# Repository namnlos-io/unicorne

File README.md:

# The Unicorne

Current revision: $Id$

A single-piece corne keyboard mod and case.

Unicorne is a Corne keyboard coupled with a hinged unibody case based on ["Corne Travel Case"](https://www.thingiverse.com/thing:4921564) by [denniskempin](https://www.thingiverse.com/denniskempin).

The Corne inside is using a single Pro Micro on the left side and a single display on the right side, the sides are part of the same matrix connected through the center hinge instead of the traditional setup with two Pro Micro's and a TRRS cable connecting the halves.

## Images

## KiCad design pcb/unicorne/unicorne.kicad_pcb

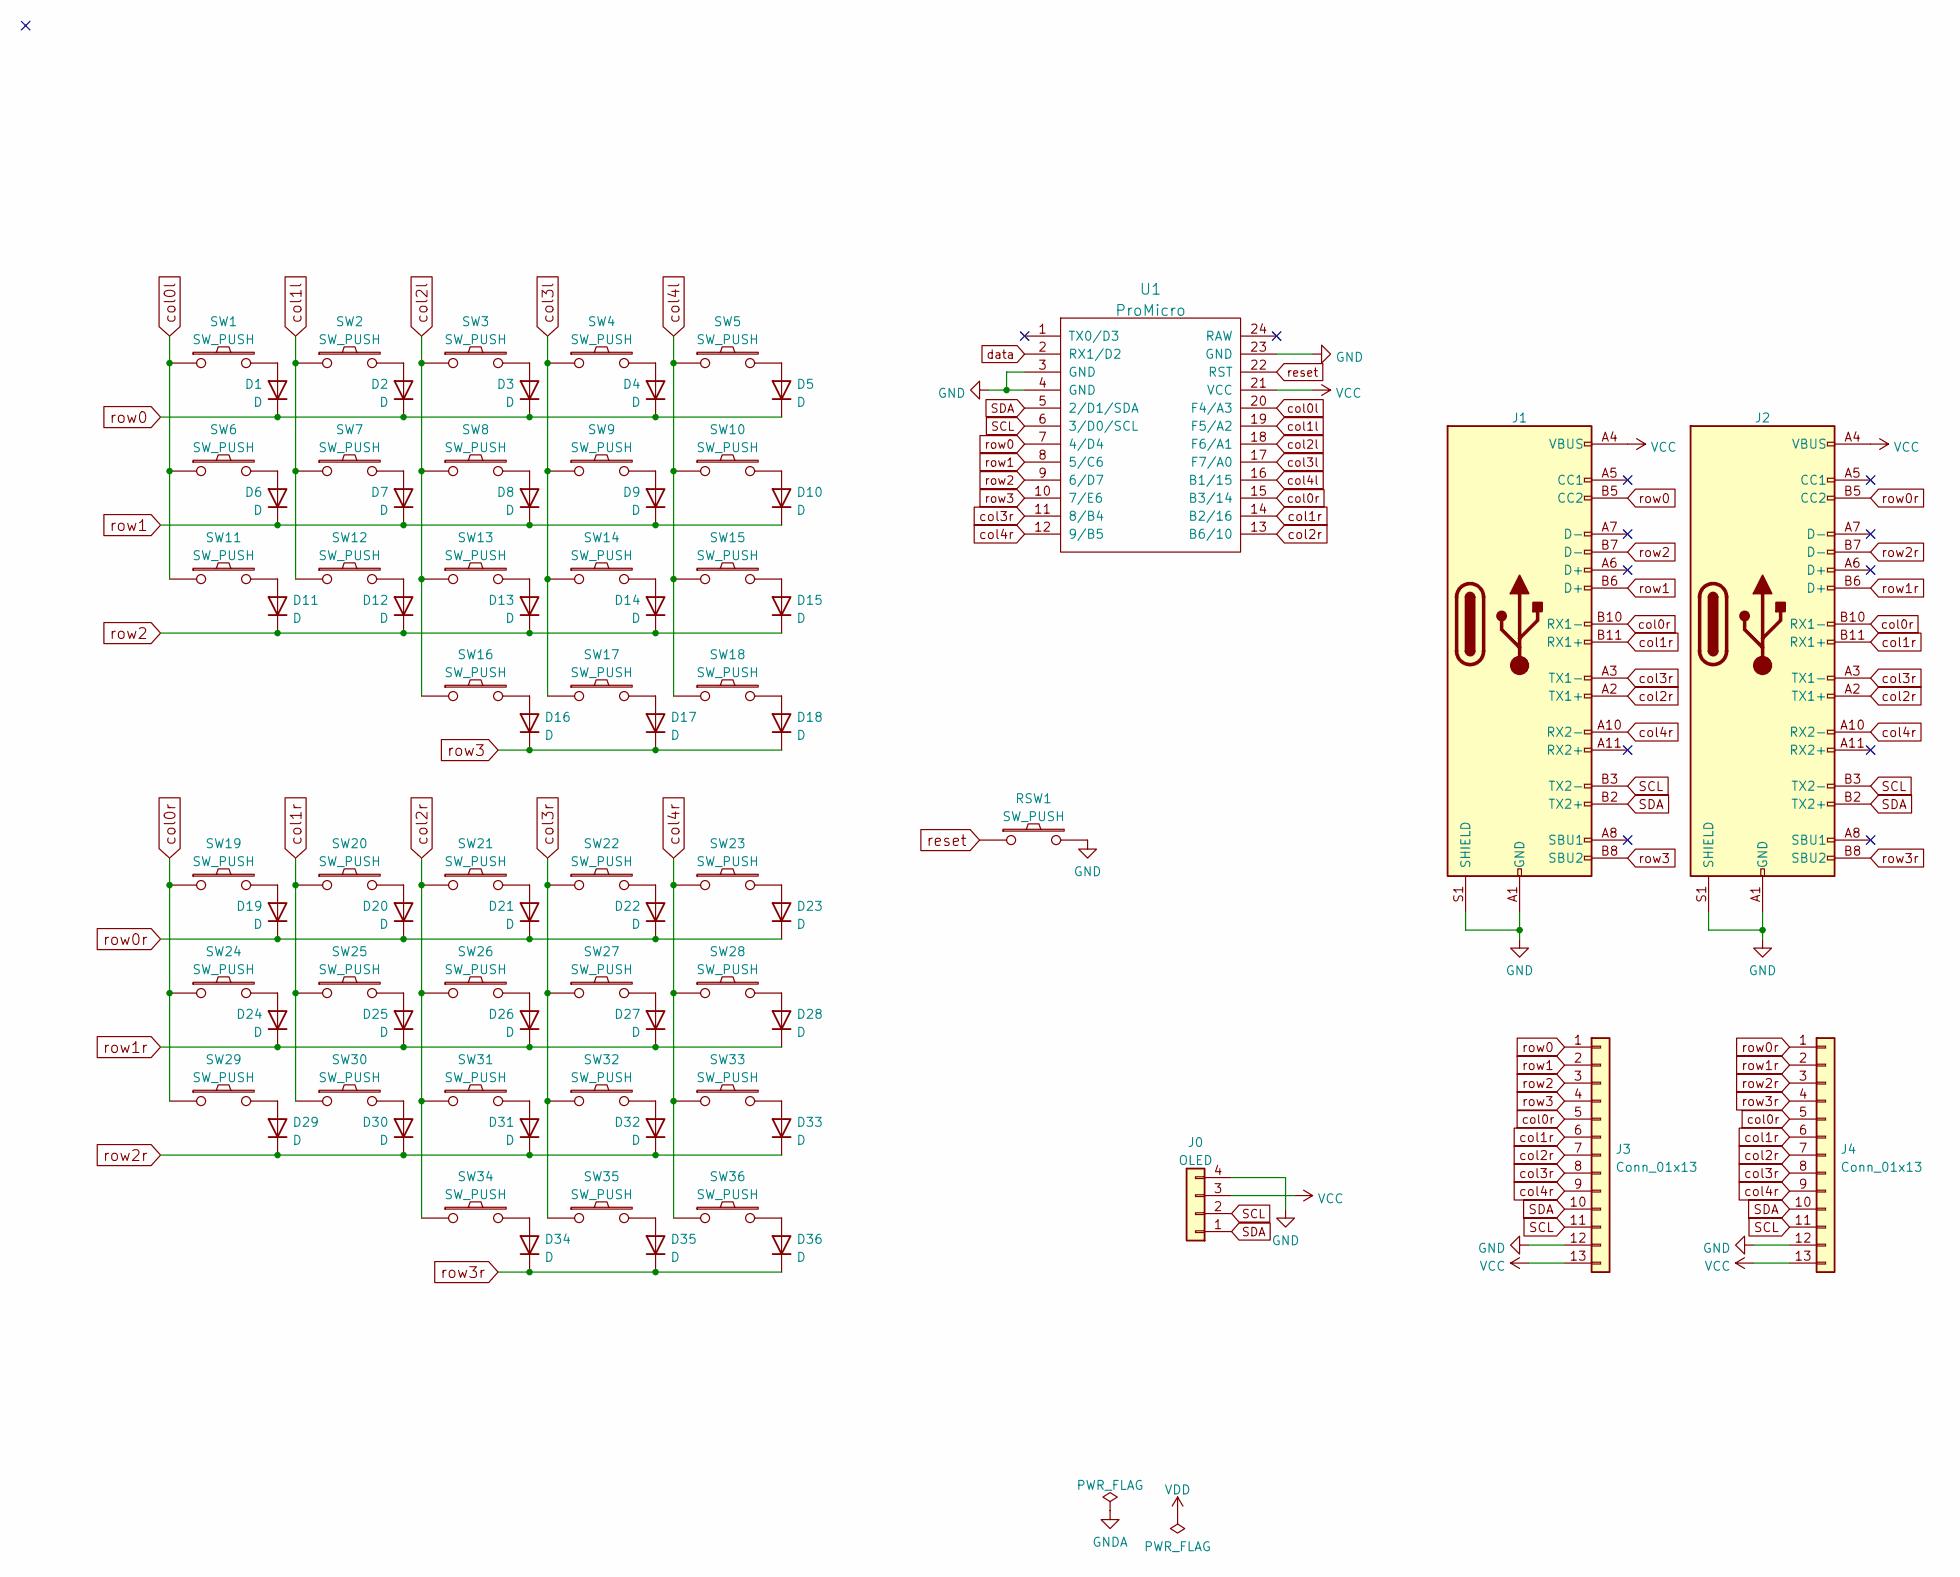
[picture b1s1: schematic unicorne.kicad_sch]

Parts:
D1, D2, D3, D4, D5, D6, D7, D8, D9, D10, D11, D12, D13, D14, D15, D16, D17, D18, D19, D20, D21, D22, D23, D24, D25, D26, D27, D28, D29, D30, D31, D32, D33, D34, D35, D36: D; D3_TH
J0: OLED; OLED_1side
J1, J2: USB_C_Receptacle; USB_C_Receptacle_Amphenol_12401548E4-2A
J3, J4: Conn_01x13; PinSocket_1x13_P1.27mm_Vertical
RSW1: SW_PUSH; ResetSW_1side
SW1, SW2, SW3, SW4, SW5, SW6, SW7, SW8, SW9, SW10, SW11, SW12, SW13, SW14, SW15, SW16, SW17, SW19, SW20, SW21, SW22, SW23, SW24, SW25, SW26, SW27, SW28, SW29, SW30, SW31, SW32, SW33, SW34, SW35: SW_PUSH; keyswitch_cherrymx_alps_choc12_1u
SW18, SW36: SW_PUSH; keyswitch_cherrymx_alps_choc12_1.5u
U1: ProMicro; ProMicro_v3

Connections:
GND: J0.4, J1.A1 (GND), J1.A12 (GND), J1.B1 (GND), J1.B12 (GND), J1.S1 (SHIELD), J2.A1 (GND), J2.A12 (GND), J2.B1 (GND), J2.B12 (GND), J2.S1 (SHIELD), J3.12, J4.12, RSW1.2, U1.3 (GND), U1.4 (GND), U1.23 (GND)
unnamed: D1.2 (A), SW1.2
unnamed: D2.2 (A), SW2.2
unnamed: D3.2 (A), SW3.2
unnamed: D4.2 (A), SW4.2
unnamed: D5.2 (A), SW5.2
unnamed: D6.2 (A), SW6.2
unnamed: D7.2 (A), SW7.2
unnamed: D8.2 (A), SW8.2
unnamed: D9.2 (A), SW9.2
unnamed: D10.2 (A), SW10.2
unnamed: D11.2 (A), SW11.2
unnamed: D12.2 (A), SW12.2
unnamed: D13.2 (A), SW13.2
unnamed: D14.2 (A), SW14.2
unnamed: D15.2 (A), SW15.2
unnamed: D16.2 (A), SW16.2
unnamed: D17.2 (A), SW17.2
unnamed: D18.2 (A), SW18.2
unnamed: D19.2 (A), SW19.2
unnamed: D20.2 (A), SW20.2
unnamed: D21.2 (A), SW21.2
unnamed: D22.2 (A), SW22.2
unnamed: D23.2 (A), SW23.2
unnamed: D24.2 (A), SW24.2
unnamed: D25.2 (A), SW25.2
unnamed: D26.2 (A), SW26.2
unnamed: D27.2 (A), SW27.2
unnamed: D28.2 (A), SW28.2
unnamed: D29.2 (A), SW29.2
unnamed: D30.2 (A), SW30.2
unnamed: D31.2 (A), SW31.2
unnamed: D32.2 (A), SW32.2
unnamed: D33.2 (A), SW33.2
unnamed: D34.2 (A), SW34.2
unnamed: D35.2 (A), SW35.2
unnamed: D36.2 (A), SW36.2
SCL: J0.2, J1.B3 (TX2-), J2.B3 (TX2-), J3.11, J4.11, U1.6 (3/D0/SCL)
SDA: J0.1, J1.B2 (TX2+), J2.B2 (TX2+), J3.10, J4.10, U1.5 (2/D1/SDA)
VCC: J0.3, J1.A4 (VBUS), J1.A9 (VBUS), J1.B4 (VBUS), J1.B9 (VBUS), J2.A4 (VBUS), J2.A9 (VBUS), J2.B4 (VBUS), J2.B9 (VBUS), J3.13, J4.13, U1.21 (VCC)
col0l: SW1.1, SW6.1, SW11.1, U1.20 (F4/A3)
col0r: J1.B10 (RX1-), J2.B10 (RX1-), J3.5, J4.5, SW19.1, SW24.1, SW29.1, U1.15 (B3/14)
col1l: SW2.1, SW7.1, SW12.1, U1.19 (F5/A2)
col1r: J1.B11 (RX1+), J2.B11 (RX1+), J3.6, J4.6, SW20.1, SW25.1, SW30.1, U1.14 (B2/16)
col2l: SW3.1, SW8.1, SW13.1, SW16.1, U1.18 (F6/A1)
col2r: J1.A2 (TX1+), J2.A2 (TX1+), J3.7, J4.7, SW21.1, SW26.1, SW31.1, SW34.1, U1.13 (B6/10)
col3l: SW4.1, SW9.1, SW14.1, SW17.1, U1.17 (F7/A0)
col3r: J1.A3 (TX1-), J2.A3 (TX1-), J3.8, J4.8, SW22.1, SW27.1, SW32.1, SW35.1, U1.11 (8/B4)
col4l: SW5.1, SW10.1, SW15.1, SW18.1, U1.16 (B1/15)
col4r: J1.A10 (RX2-), J2.A10 (RX2-), J3.9, J4.9, SW23.1, SW28.1, SW33.1, SW36.1, U1.12 (9/B5)
data: U1.2 (RX1/D2)
reset: RSW1.1, U1.22 (RST)
row0: D1.1 (K), D2.1 (K), D3.1 (K), D4.1 (K), D5.1 (K), J1.B5 (CC2), J3.1, U1.7 (4/D4)
row0r: D19.1 (K), D20.1 (K), D21.1 (K), D22.1 (K), D23.1 (K), J2.B5 (CC2), J4.1
row1: D6.1 (K), D7.1 (K), D8.1 (K), D9.1 (K), D10.1 (K), J1.B6 (D+), J3.2, U1.8 (5/C6)
row1r: D24.1 (K), D25.1 (K), D26.1 (K), D27.1 (K), D28.1 (K), J2.B6 (D+), J4.2
row2: D11.1 (K), D12.1 (K), D13.1 (K), D14.1 (K), D15.1 (K), J1.B7 (D-), J3.3, U1.9 (6/D7)
row2r: D29.1 (K), D30.1 (K), D31.1 (K), D32.1 (K), D33.1 (K), J2.B7 (D-), J4.3
row3: D16.1 (K), D17.1 (K), D18.1 (K), J1.B8 (SBU2), J3.4, U1.10 (7/E6)
row3r: D34.1 (K), D35.1 (K), D36.1 (K), J2.B8 (SBU2), J4.4

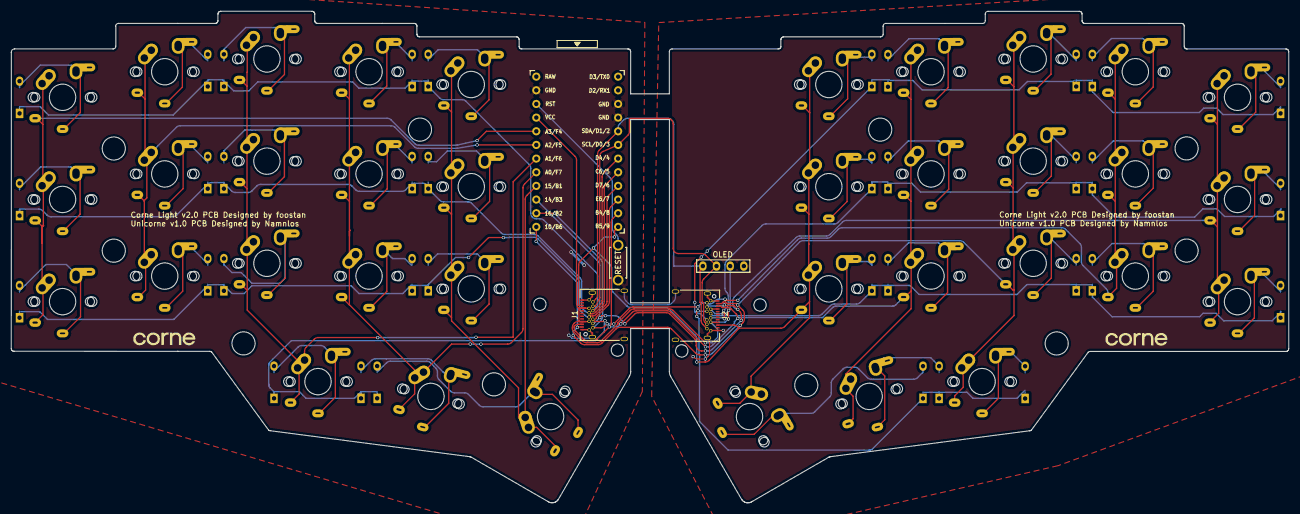
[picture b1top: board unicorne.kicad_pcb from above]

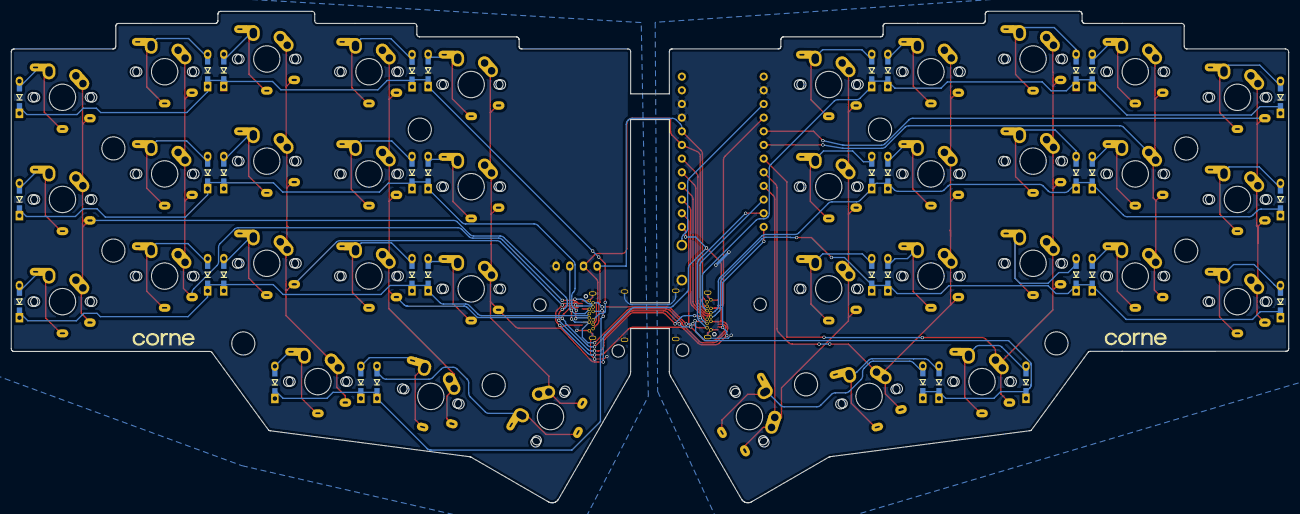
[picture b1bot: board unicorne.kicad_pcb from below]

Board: 2 copper layers, 237.5 x 91.4 mm, 91 parts (48 on the bottom side), 59 nets.

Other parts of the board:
Ref**: Val**; thread_m2
Ref**#2, Ref**#6, Ref**#7: Val**; thread_m2
Ref**#3, Ref**#4, Ref**#5, Ref**#8, Ref**#9, Ref**#10, Ref**#11, Ref**#12, Ref**#13, Ref**#14: Val**; spacer_m2

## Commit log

2022-05-05 Initial commit.
2022-05-05 First revision and renders.
2022-05-05 Preparing version 0.1
2022-05-05 Some updates and preparing for the future.
2022-05-05 Some more preparations.
2022-05-08 Custom PCB for the Unicorne based on Corne Light.
